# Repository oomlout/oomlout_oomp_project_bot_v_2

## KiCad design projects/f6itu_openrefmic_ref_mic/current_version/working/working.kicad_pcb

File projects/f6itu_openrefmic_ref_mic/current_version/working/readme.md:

# openrefmic
 
## summary 
* id: f6itu_openrefmic_ref_mic
* user: f6itu
* name: openrefmic
* board: ref_mic
* repo: https://github.com/F6ITU/OpenRefMic
* src_file_repo_kicad_pcb: preamplifier/ref_mic/ref_mic.kicad_pcb
* src_file_repo_kicad_pcb_link: https://github.com/F6ITU/OpenRefMic/tree/main/preamplifier/ref_mic/ref_mic.kicad_pcb
* src_file_repo_kicad_sch: preamplifier/ref_mic/ref_mic.kicad_sch
* src_file_repo_kicad_sch_link: https://github.com/F6ITU/OpenRefMic/tree/main/preamplifier/ref_mic/ref_mic.kicad_sch

* src_file_repo_sch: 
* src_file_repo_sch_link: https://github.com/F6ITU/OpenRefMic/tree/main/
* full details link: https://github.com/oomlout/oomlout_oomp_project_bot_v_2/tree/main/projects/f6itu_openrefmic_ref_mic/current_version/working

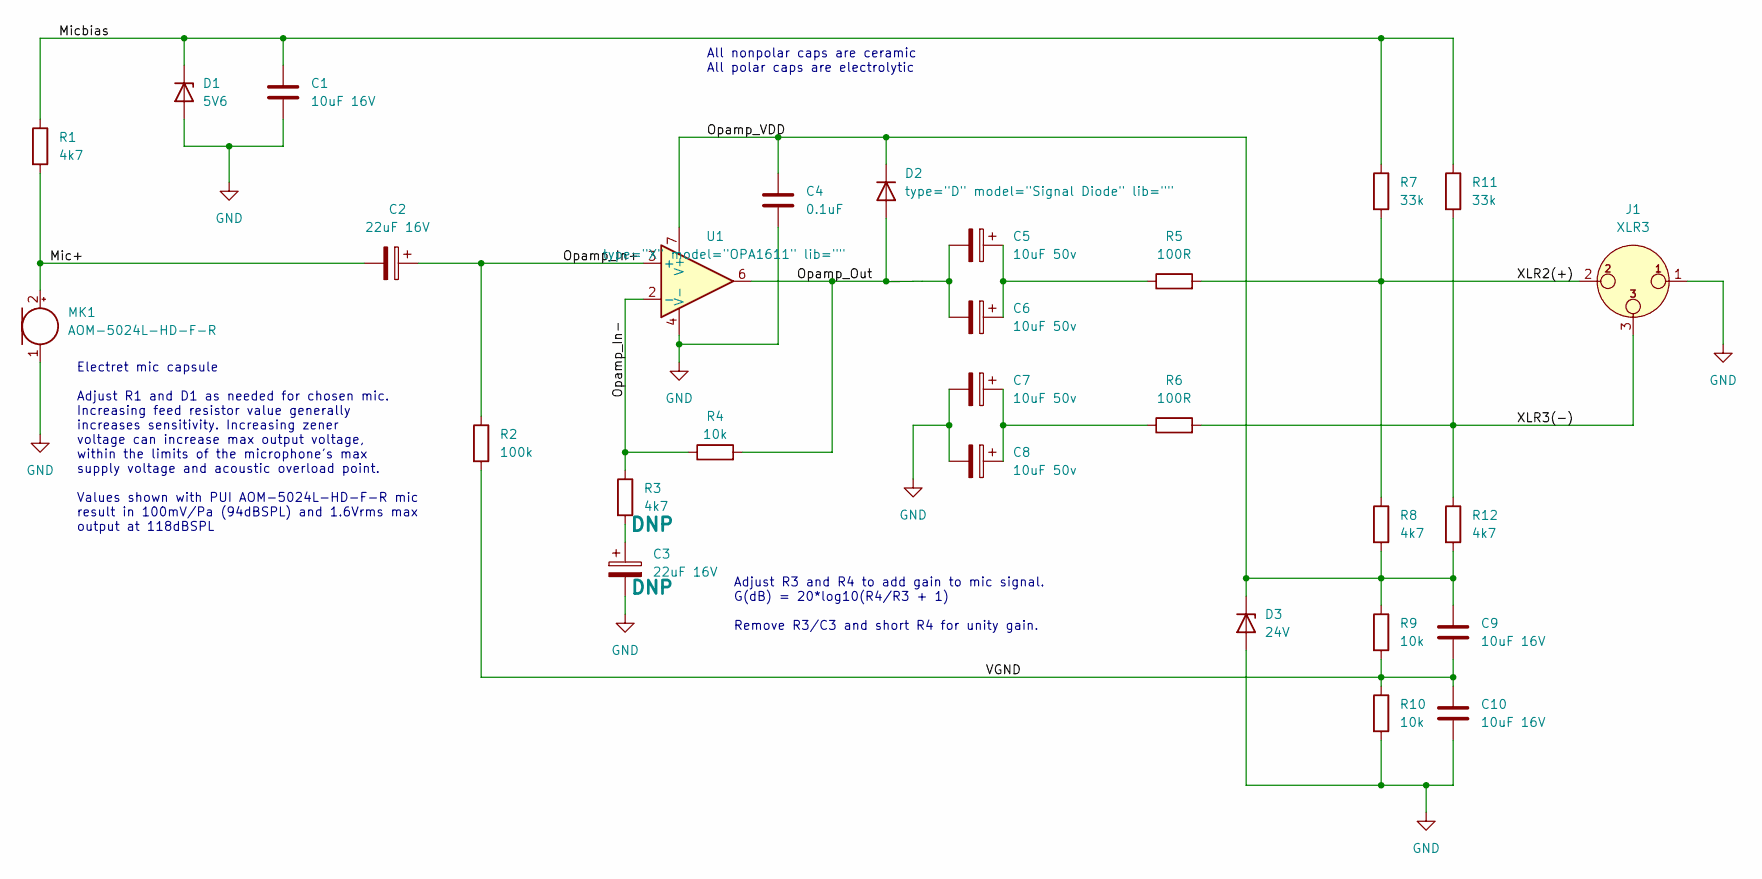
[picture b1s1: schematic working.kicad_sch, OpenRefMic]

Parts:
C1, C9, C10: 10uF 16V; C_0805_2012Metric_Pad1.18x1.45mm_HandSolder
C2, C3: 22uF 16V; CP_Elec_5x5.4
C4: 0.1uF; C_0603_1608Metric_Pad1.08x0.95mm_HandSolder
C5, C6, C7, C8: 10uF 50v; CP_Elec_6.3x5.4_Nichicon
D1: 5V6; SC-59_Handsoldering
D2: type="D" model="Signal Diode" lib=""; SOT-23_Handsoldering
D3: 24V; SOT-23_Handsoldering
J1: XLR3; PinHeader_1x03_P2.54mm_Vertical
MK1: AOM-5024L-HD-F-R; PinHeader_1x02_P2.54mm_Vertical
R1, R3, R8, R12: 4k7; R_0603_1608Metric_Pad0.98x0.95mm_HandSolder
R2: 100k; R_0603_1608Metric_Pad0.98x0.95mm_HandSolder
R4, R9, R10: 10k; R_0603_1608Metric_Pad0.98x0.95mm_HandSolder
R5, R6: 100R; R_0603_1608Metric_Pad0.98x0.95mm_HandSolder
R7, R11: 33k; R_0603_1608Metric_Pad0.98x0.95mm_HandSolder
U1: type="X" model="OPA1611" lib=""; SOIC-8_3.9x4.9mm_P1.27mm

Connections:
/Mic+: C2.2, MK1.2 (+), R1.2; also elsewhere on the board
/Micbias: C1.1, D1.3 (K), R1.1, R7.1, R11.1
/Opamp_In+: C2.1, R2.1, U1.3 (+)
/Opamp_In-: R3.1, R4.1, U1.2 (-)
/Opamp_Out: C5.2, C6.2, D2.1 (A), R4.2, U1.6
/Opamp_VDD: C4.1, C9.1, D2.3 (K), D3.3 (K), R8.2, R9.1, R12.2, U1.7 (V+)
/VGND: C9.2, C10.1, R2.2, R9.2, R10.1
/XLR2(+): J1.2, R5.2, R7.2, R8.1; also elsewhere on the board
/XLR3(-): J1.3, R6.2, R11.2, R12.1; also elsewhere on the board
GND: C1.2, C3.2, C4.2, C7.2, C8.2, C10.2, D1.1 (A), D3.1 (A), J1.1, MK1.1 (-), R10.2, U1.4 (V-); also elsewhere on the board
unnamed: C3.1, R3.2
unnamed: C5.1, C6.1, R5.1
unnamed: C7.1, C8.1, R6.1

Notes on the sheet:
All nonpolar caps are ceramic All polar caps are electrolytic
Adjust R3 and R4 to add gain to mic signal. G(dB) = 20*log10(R4/R3 + 1) Remove R3/C3 and short R4 for unity gain.
Electret mic capsule Adjust R1 and D1 as needed for chosen mic. Increasing feed resistor value generally increases sensitivity. Increasing zener voltage can increase max output voltage, within the limits of the microphone's max supply voltage and acoustic overload point. Values shown with PUI AOM-5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

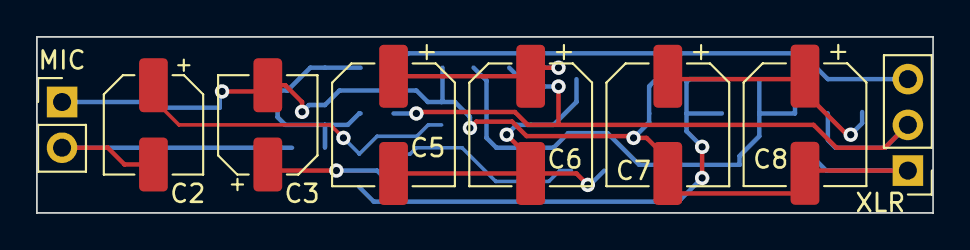
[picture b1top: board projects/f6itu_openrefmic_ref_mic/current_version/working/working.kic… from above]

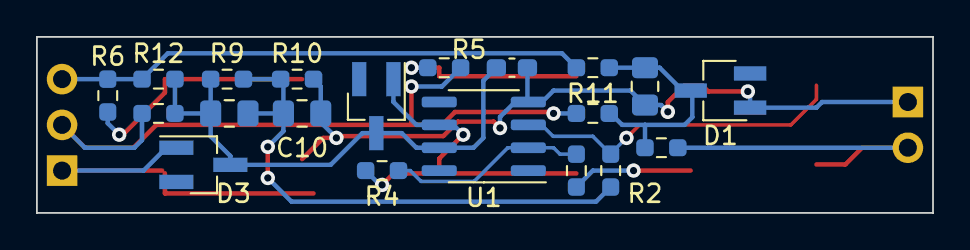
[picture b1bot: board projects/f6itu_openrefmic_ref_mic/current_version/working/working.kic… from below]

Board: 2 copper layers, 49.8 x 9.8 mm, 28 parts (20 on the bottom side), 13 nets.

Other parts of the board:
MIC: Microphone; PinHeader_1x02_P2.54mm_Vertical
XLR: XLR3; PinHeader_1x03_P2.54mm_Vertical

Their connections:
/Mic+: MIC.2 (+); also elsewhere on the board
/XLR2(+): XLR.2; also elsewhere on the board
/XLR3(-): XLR.3; also elsewhere on the board
GND: MIC.1 (-), XLR.1; also elsewhere on the board

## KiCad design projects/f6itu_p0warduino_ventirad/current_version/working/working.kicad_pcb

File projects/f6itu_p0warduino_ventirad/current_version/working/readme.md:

# p0warduino
 
## summary 
* id: f6itu_p0warduino_ventirad
* user: f6itu
* name: p0warduino
* board: ventirad
* repo: https://github.com/F6ITU/P0wArduino
* src_file_repo_kicad_pcb: ventirad.kicad_pcb
* src_file_repo_kicad_pcb_link: https://github.com/F6ITU/P0wArduino/tree/master/ventirad.kicad_pcb

* src_file_repo_sch: ventirad.sch
* src_file_repo_sch_link: https://github.com/F6ITU/P0wArduino/tree/master/ventirad.sch
* full details link: https://github.com/oomlout/oomlout_oomp_project_bot_v_2/tree/main/projects/f6itu_p0warduino_ventirad/current_version/working

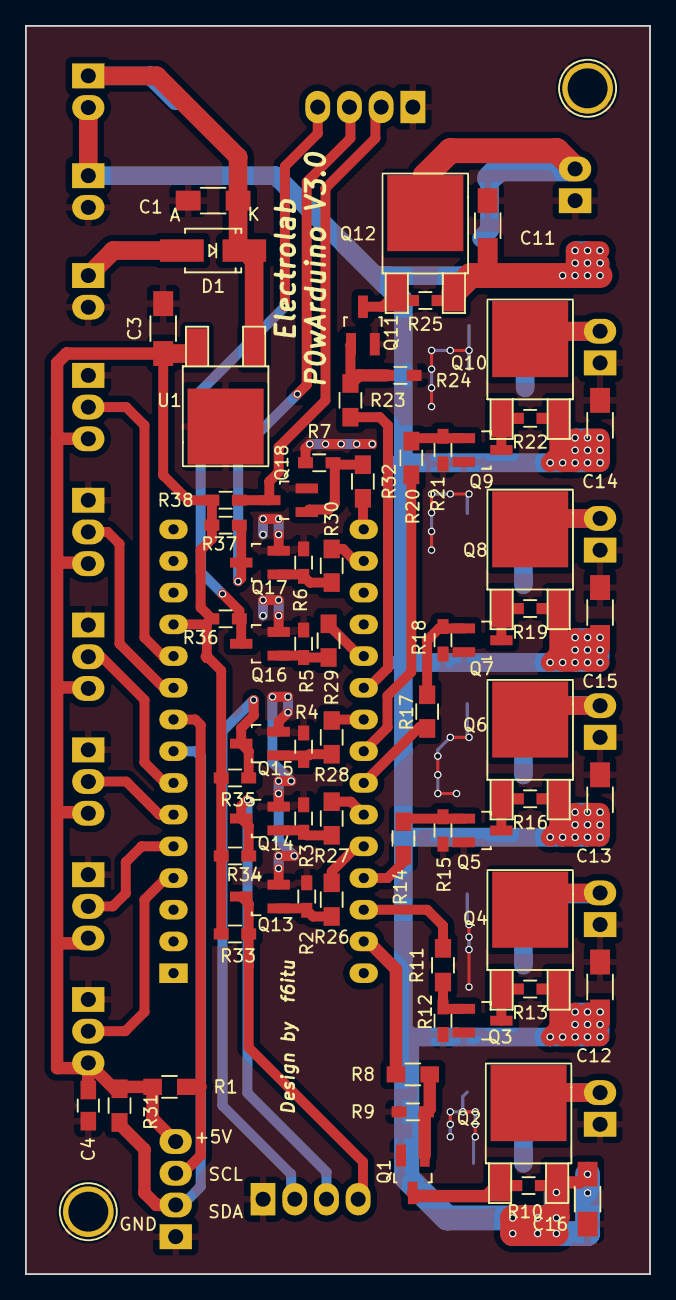
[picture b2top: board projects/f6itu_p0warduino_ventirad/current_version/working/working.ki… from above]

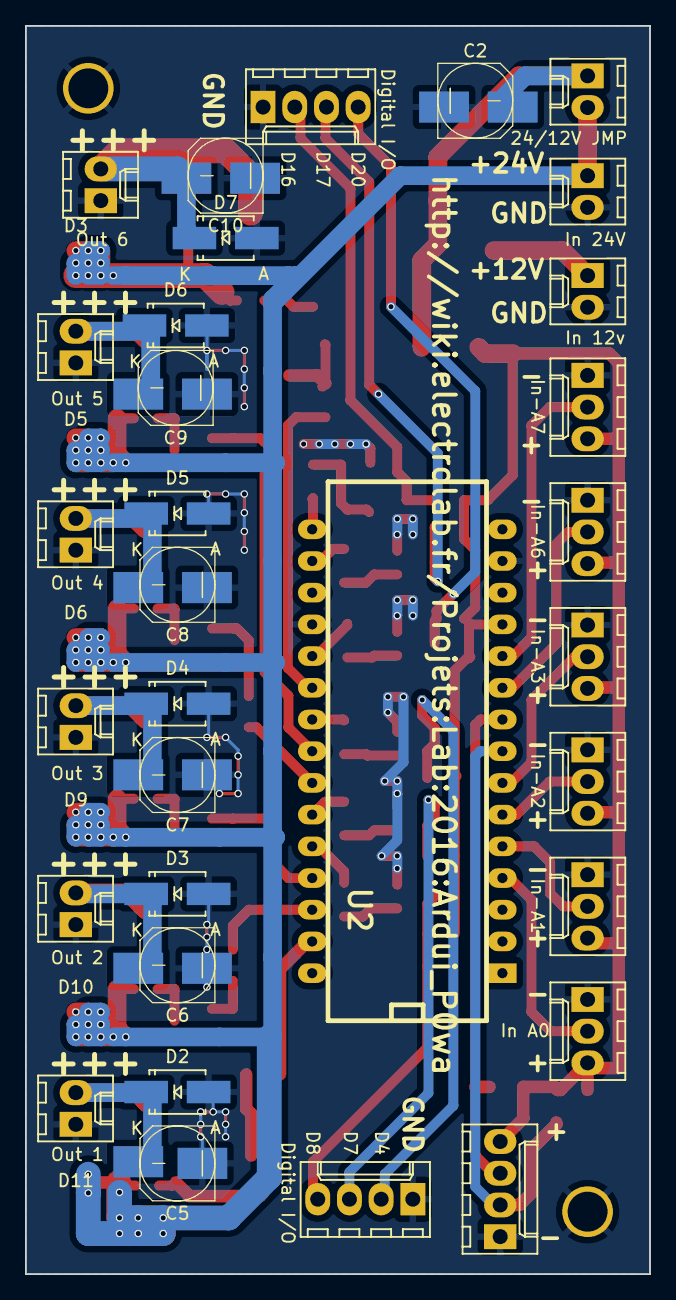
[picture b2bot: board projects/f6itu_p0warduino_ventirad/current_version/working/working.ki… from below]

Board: 2 copper layers, 50.0 x 100.0 mm, 81 parts (14 on the bottom side), 48 nets.

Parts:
C1, C3, C11, C12, C13, C14, C15, C16: 100n; C_1206_HandSoldering
C2: 200u; c_elec_6.3x7.7
C4: 10n; C_0805_HandSoldering
C5, C6, C7, C8, C9, C10: 100u; c_elec_6.3x7.7
D1, D2, D3, D4, D5, D6, D7: SS-26; SMA_Handsoldering
Q1, Q3, Q5, Q7, Q9, Q11, Q13, Q14, Q15, Q16, Q17, Q18: 2N7000; SOT-23_Handsoldering
Q2, Q4, Q6, Q8, Q10, Q12: IRFR9014; TO-252-2Lead
R1, R31: 10k; R_0805_HandSoldering
R2, R3, R4, R5, R6, R7, R9, R10, R12, R13, R15, R16, R18, R19, R21, R22, R24, R25, R33, R34, R35, R36, R37, R38: 10k; R_0603_HandSoldering
R8, R11, R14, R17, R20, R23, R26, R27, R28, R29, R30, R32: 1k; R_0805_HandSoldering
U1: LM7805; TO-252-2Lead
U2: http://wiki.electrolab.fr/Projets:Lab:2016:Ardui_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; arduino_nano

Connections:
+5V: C3.1, C4.1, R1.2, R31.2, R33.1, R34.1, R35.1, R36.1, R37.1, R38.1, U1.3, U2.12
+12V: C1.1, C2.1, D1.1, U1.1
GND: C1.2, C2.2, C3.2, C4.2, C5.2, C6.2, C7.2, C8.2, C9.2, C10.2, C11.1, C12.1, C13.1, C14.1, C15.1, C16.1, D2.2, D3.2, D4.2, D5.2, D6.2, D7.2, Q1.2, Q3.2, Q5.2, Q7.2, Q9.2, Q11.2, Q13.2, Q14.2, Q15.2, Q16.2, Q17.2, Q18.2, R2.2, R3.2, R4.2, R5.2, R6.2, R7.2, R9.2, R12.2, R15.2, R18.2, R21.2, R24.2, U1.2, U2.14, U2.19
unnamed: C5.1, D2.1, Q2.2
unnamed: C6.1, D3.1, Q4.2
unnamed: C7.1, D4.1, Q6.2
unnamed: C8.1, D5.1, Q8.2
unnamed: C9.1, D6.1, Q10.2
unnamed: C10.1, D7.1, Q12.2
unnamed: C11.2, C12.2, C13.2, C14.2, C15.2, C16.2, Q2.3, Q4.3, Q6.3, Q8.3, Q10.3, Q12.3, R10.1, R13.1, R16.1, R19.1, R22.1, R25.1
unnamed: R31.1, U2.8
unnamed: R1.1, U2.9
unnamed: Q15.3, R35.2
unnamed: Q14.3, R34.2
unnamed: Q13.3, R33.2
unnamed: Q18.3, R38.2
unnamed: Q17.3, R37.2
unnamed: Q16.3, R36.2
unnamed: Q1.1, R8.1, R9.1
unnamed: Q1.3, Q2.1, R10.2
unnamed: Q3.1, R11.1, R12.1
unnamed: Q3.3, Q4.1, R13.2
unnamed: Q5.1, R14.1, R15.1
unnamed: Q5.3, Q6.1, R16.2
unnamed: Q7.1, R17.1, R18.1
unnamed: Q7.3, Q8.1, R19.2
unnamed: Q9.1, R20.1, R21.1
unnamed: Q9.3, Q10.1, R22.2
unnamed: Q11.1, R23.1, R24.1
unnamed: Q11.3, Q12.1, R25.2
unnamed: Q13.1, R2.1, R26.1
unnamed: Q14.1, R3.1, R27.1
unnamed: Q15.1, R4.1, R28.1
unnamed: Q16.1, R5.1, R29.1
unnamed: Q17.1, R6.1, R30.1
unnamed: Q18.1, R7.1, R32.1
unnamed: R8.2, U2.29
unnamed: R11.2, U2.28
unnamed: R14.2, U2.27
unnamed: R17.2, U2.24
unnamed: R20.2, U2.23
unnamed: R23.2, U2.21
unnamed: R26.2, U2.26
unnamed: R27.2, U2.25
unnamed: R28.2, U2.22
unnamed: R29.2, U2.20
unnamed: R30.2, U2.17
unnamed: R32.2, U2.16

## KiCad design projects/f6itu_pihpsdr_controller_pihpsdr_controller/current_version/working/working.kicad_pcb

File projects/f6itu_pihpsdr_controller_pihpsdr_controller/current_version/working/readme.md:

# pihpsdr_controller
 
## summary 
* id: f6itu_pihpsdr_controller_pihpsdr_controller
* user: f6itu
* name: pihpsdr_controller
* board: pihpsdr_controller
* repo: https://github.com/F6ITU/piHPSDR_Controller
* src_file_repo_kicad_pcb: piHPSDR_Controller.kicad_pcb
* src_file_repo_kicad_pcb_link: https://github.com/F6ITU/piHPSDR_Controller/tree/master/piHPSDR_Controller.kicad_pcb

* src_file_repo_sch: 
* src_file_repo_sch_link: https://github.com/F6ITU/piHPSDR_Controller/tree/master/
* full details link: https://github.com/oomlout/oomlout_oomp_project_bot_v_2/tree/main/projects/f6itu_pihpsdr_controller_pihpsdr_controller/current_version/working

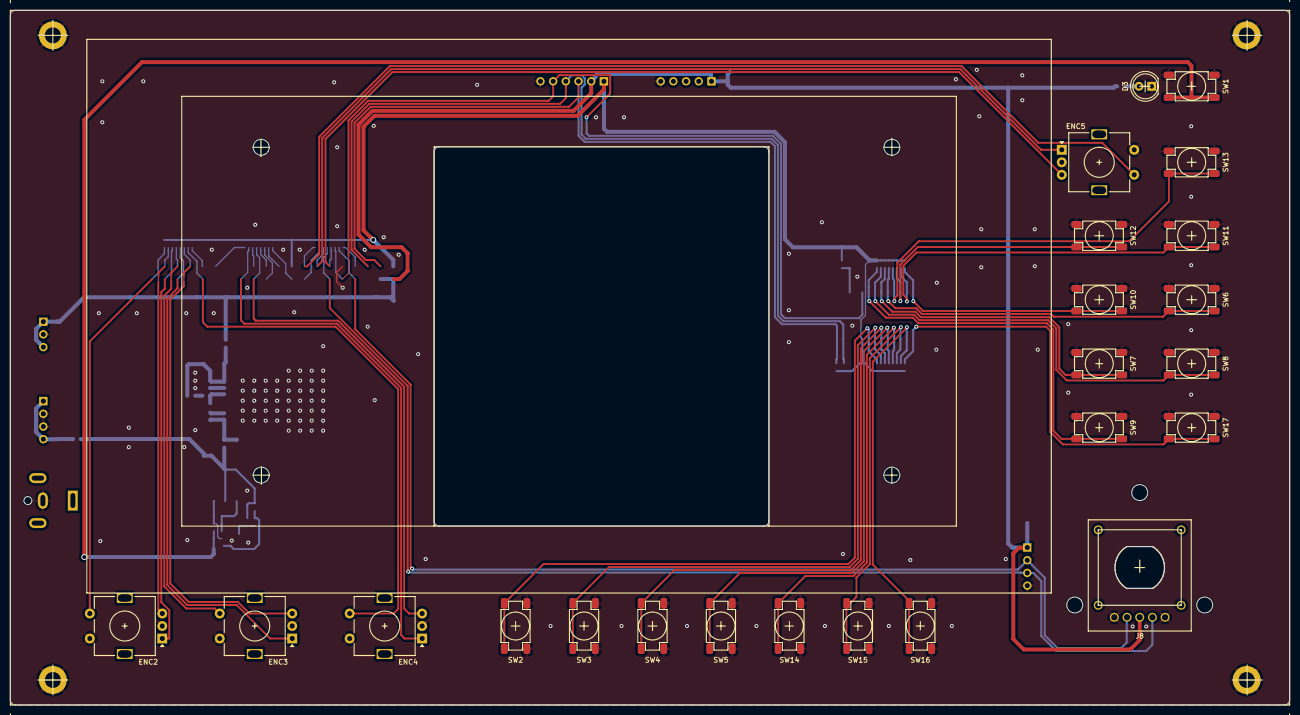
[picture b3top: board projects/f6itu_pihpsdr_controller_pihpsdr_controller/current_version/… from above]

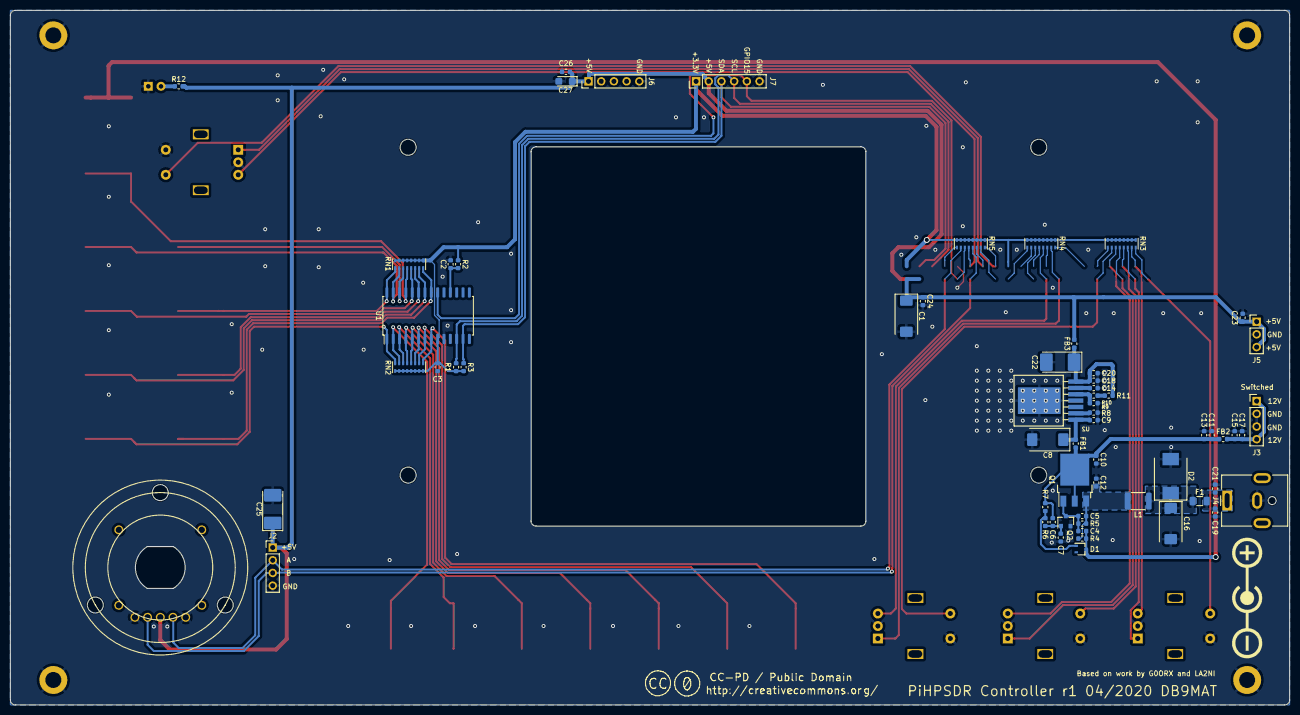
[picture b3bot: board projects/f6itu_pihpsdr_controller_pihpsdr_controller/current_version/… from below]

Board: 2 copper layers, 256.0 x 139.0 mm, 88 parts (61 on the bottom side), 53 nets.

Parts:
 : MountingHole_3.2mm_M3_DIN965_Pad
 #2,  #3,  #4: MountingHole_3.2mm_M3_DIN965_Pad
C1: 220u/10V; CP_EIA-7343-31_Kemet-D
C2: 1n; C_0603_1608Metric
C3, C10, C12, C20, C21, C24, C26: 10u; C_0603_1608Metric
C4, C13, C17: 1u; C_0603_1608Metric
C5, C6, C7, C9, C11, C14, C15, C18, C19, C23: 100n; C_0603_1608Metric
C8: 47u/35V; CP_EIA-7343-43_Kemet-X
C16: 22u/35V; CP_EIA-7343-31_Kemet-D
C22, C25: 100u/10V; CP_EIA-7132-28_AVX-C
C27: 100u/6.3V; CP_EIA-3216-18_Kemet-A
D1: BAS16J; SOT-323_SC-70
D2: SK54; D_SMC
D3: Green; LED_D5.0mm
ENC2, ENC3, ENC4, ENC5: Rotary_Encoder_Switch; RotaryEncoder_Alps_EC11E-Switch_Vertical_H20mm
F1: 5A; Fuse_1206_3216Metric
FB1, FB2, FB3: TBD; L_0603_1608Metric
J2: ENC1; PinHeader_1x04_P2.54mm_Vertical
J3: 12V_SWITCHED; PinHeader_1x04_P2.54mm_Vertical
J4: 12V_IN; BarrelJack_CUI_PJ-063AH_Horizontal
J5: 5V/3A; PinHeader_1x03_P2.54mm_Vertical
J6: TO_DISPLAY; PinHeader_1x05_P2.54mm_Vertical
J7: Conn_01x06; PinHeader_1x06_P2.54mm_Vertical
J8: ENC1a; HRPG-AXXX
L1: 74279226101; L_1812_4532Metric
Q1: FDD6685; TO-252-3_TabPin2
Q2: 2N7002K; SOT-23
R1, R3, R4: 10k; R_0603_1608Metric
R2, R5, R7: 100k; R_0603_1608Metric
R6: 180k; R_0603_1608Metric
R8, R12: 1k5; R_0603_1608Metric
R9: 620; R_0603_1608Metric
R10: 3k3; R_0603_1608Metric
R11: 47; R_0603_1608Metric
RN1, RN2, RN3, RN4, RN5: 10k; R_Cat16-8
SW1: ON_OFF; TL3301AF160QG
SW2, SW3, SW4, SW5, SW6, SW7, SW8, SW9, SW10, SW11, SW12, SW13, SW14, SW15, SW16, SW17: SW_Push; TL3301AF160QG
U1: MCP23017_SO; SOIC-28W_7.5x17.9mm_P1.27mm
U2: LMZ22005; 7TO-PMOD

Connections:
+3V3: C3.1, J7.1, R1.2, R2.1, R3.1, RN1.1, RN2.1, RN3.1, RN4.1, RN5.1, U1.9
+5V: C1.1, C23.1, C24.1, C25.1, C26.1, C27.1, FB3.2, J2.1, J5.1, J5.3, J6.1, J7.2, J8.3, R12.2
+12V: C6.1, C10.1, C11.1, C13.1, FB1.2, FB2.2, Q1.2, R7.1
/Raspberry Pi/GPIO2: J7.3, R3.2, U1.13
/Raspberry Pi/GPIO3: J7.4, R1.1, U1.12
GND: .1, #2.1, #3.1, #4.1, C1.2, C2.2, C3.2, C7.2, C8.2, C9.2, C10.2, C11.2, C12.2, C13.2, C14.2, C15.2, C16.2, C17.2, C18.2, C19.2, C20.2, C21.2, C22.2, C23.2, C24.2, C25.2, C26.2, C27.2, D2.2, D3.1, ENC2.C, ENC2.S2, ENC3.C, ENC3.S2, ENC4.C, ENC4.S2, ENC5.C, ENC5.S2, J2.4, J3.2, J3.3, J4.2, J5.2, J6.5, J7.6, J8.1, J8.5, Q2.2, R8.1, R9.1, SW1.1, SW2.1, SW3.1, SW4.1, SW5.1, SW6.1, SW7.1, SW8.1, SW9.1, SW10.1, SW11.1, SW12.1, SW13.1, SW14.1, SW15.1, SW16.1, SW17.1, U1.10, U2.4, U2.8
GPA0: RN1.2, SW9.2, U1.21
GPA1: RN1.3, SW8.2, U1.22
GPA2: RN1.4, SW7.2, U1.23
GPA3: RN1.5, SW6.2, U1.24
GPA4: RN1.6, SW13.2, U1.25
GPA5: RN1.7, SW12.2, U1.26
GPA6: RN1.8, SW11.2, U1.27
GPA7: RN1.9, SW10.2, U1.28
GPB0: RN2.2, SW17.2, U1.1
GPB1: RN2.3, SW16.2, U1.2
GPB2: RN2.4, SW15.2, U1.3
GPB3: RN2.5, SW14.2, U1.4
GPB4: RN2.6, SW5.2, U1.5
GPB5: RN2.7, SW4.2, U1.6
GPB6: RN2.8, SW3.2, U1.7
GPB7: RN2.9, SW2.2, U1.8
GPIO7: ENC4.A, RN4.3
GPIO8: ENC4.B, RN4.5
GPIO12: ENC4.S1, RN3.8
GPIO13: ENC3.B, RN3.7
GPIO14: J2.2, J8.4, RN5.8
GPIO15: J7.5, RN5.7, U1.20
GPIO16: ENC3.A, RN3.6
GPIO17: ENC5.B, RN5.6
GPIO18: J2.3, J8.2, RN5.5
GPIO19: ENC3.S1, RN3.5
GPIO20: ENC2.A, RN3.4
GPIO21: ENC2.S1, RN3.2
GPIO22: ENC5.S1, RN5.2
GPIO26: ENC2.B, RN3.3
GPIO27: ENC5.A, RN5.4
unnamed: C2.1, R2.2, U1.18
unnamed: C4.1, C5.2, Q1.1, Q2.3, R5.2
unnamed: C4.2, D1.3, R4.2, SW1.2
unnamed: C6.2, C7.1, Q2.1, R6.2
unnamed: C8.1, C9.1, FB1.1, U2.1
unnamed: C5.1, C12.1, L1.1, Q1.3, R4.1, R5.1
unnamed: C14.1, U2.6
unnamed: C15.1, C17.1, FB2.1, J3.1, J3.4
unnamed: C16.1, D2.1, F1.1, L1.2
unnamed: C18.1, C20.1, C22.1, FB3.1, R11.2, U2.7
unnamed: C19.1, C21.1, F1.2, J4.1
unnamed: D1.1, R6.1, R7.2
unnamed: D3.2, R12.1
unnamed: R8.2, U2.2
unnamed: R9.2, R10.1, U2.5
unnamed: R10.2, R11.1

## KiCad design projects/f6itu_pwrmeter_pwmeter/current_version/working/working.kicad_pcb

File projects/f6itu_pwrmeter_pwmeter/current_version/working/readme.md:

# pwrmeter
 
## summary 
* id: f6itu_pwrmeter_pwmeter
* user: f6itu
* name: pwrmeter
* board: pwmeter
* repo: https://github.com/F6ITU/PWRmeter
* src_file_repo_kicad_pcb: PWMeter.kicad_pcb
* src_file_repo_kicad_pcb_link: https://github.com/F6ITU/PWRmeter/tree/master/PWMeter.kicad_pcb

* src_file_repo_sch: PWMeter.sch
* src_file_repo_sch_link: https://github.com/F6ITU/PWRmeter/tree/master/PWMeter.sch
* full details link: https://github.com/oomlout/oomlout_oomp_project_bot_v_2/tree/main/projects/f6itu_pwrmeter_pwmeter/current_version/working

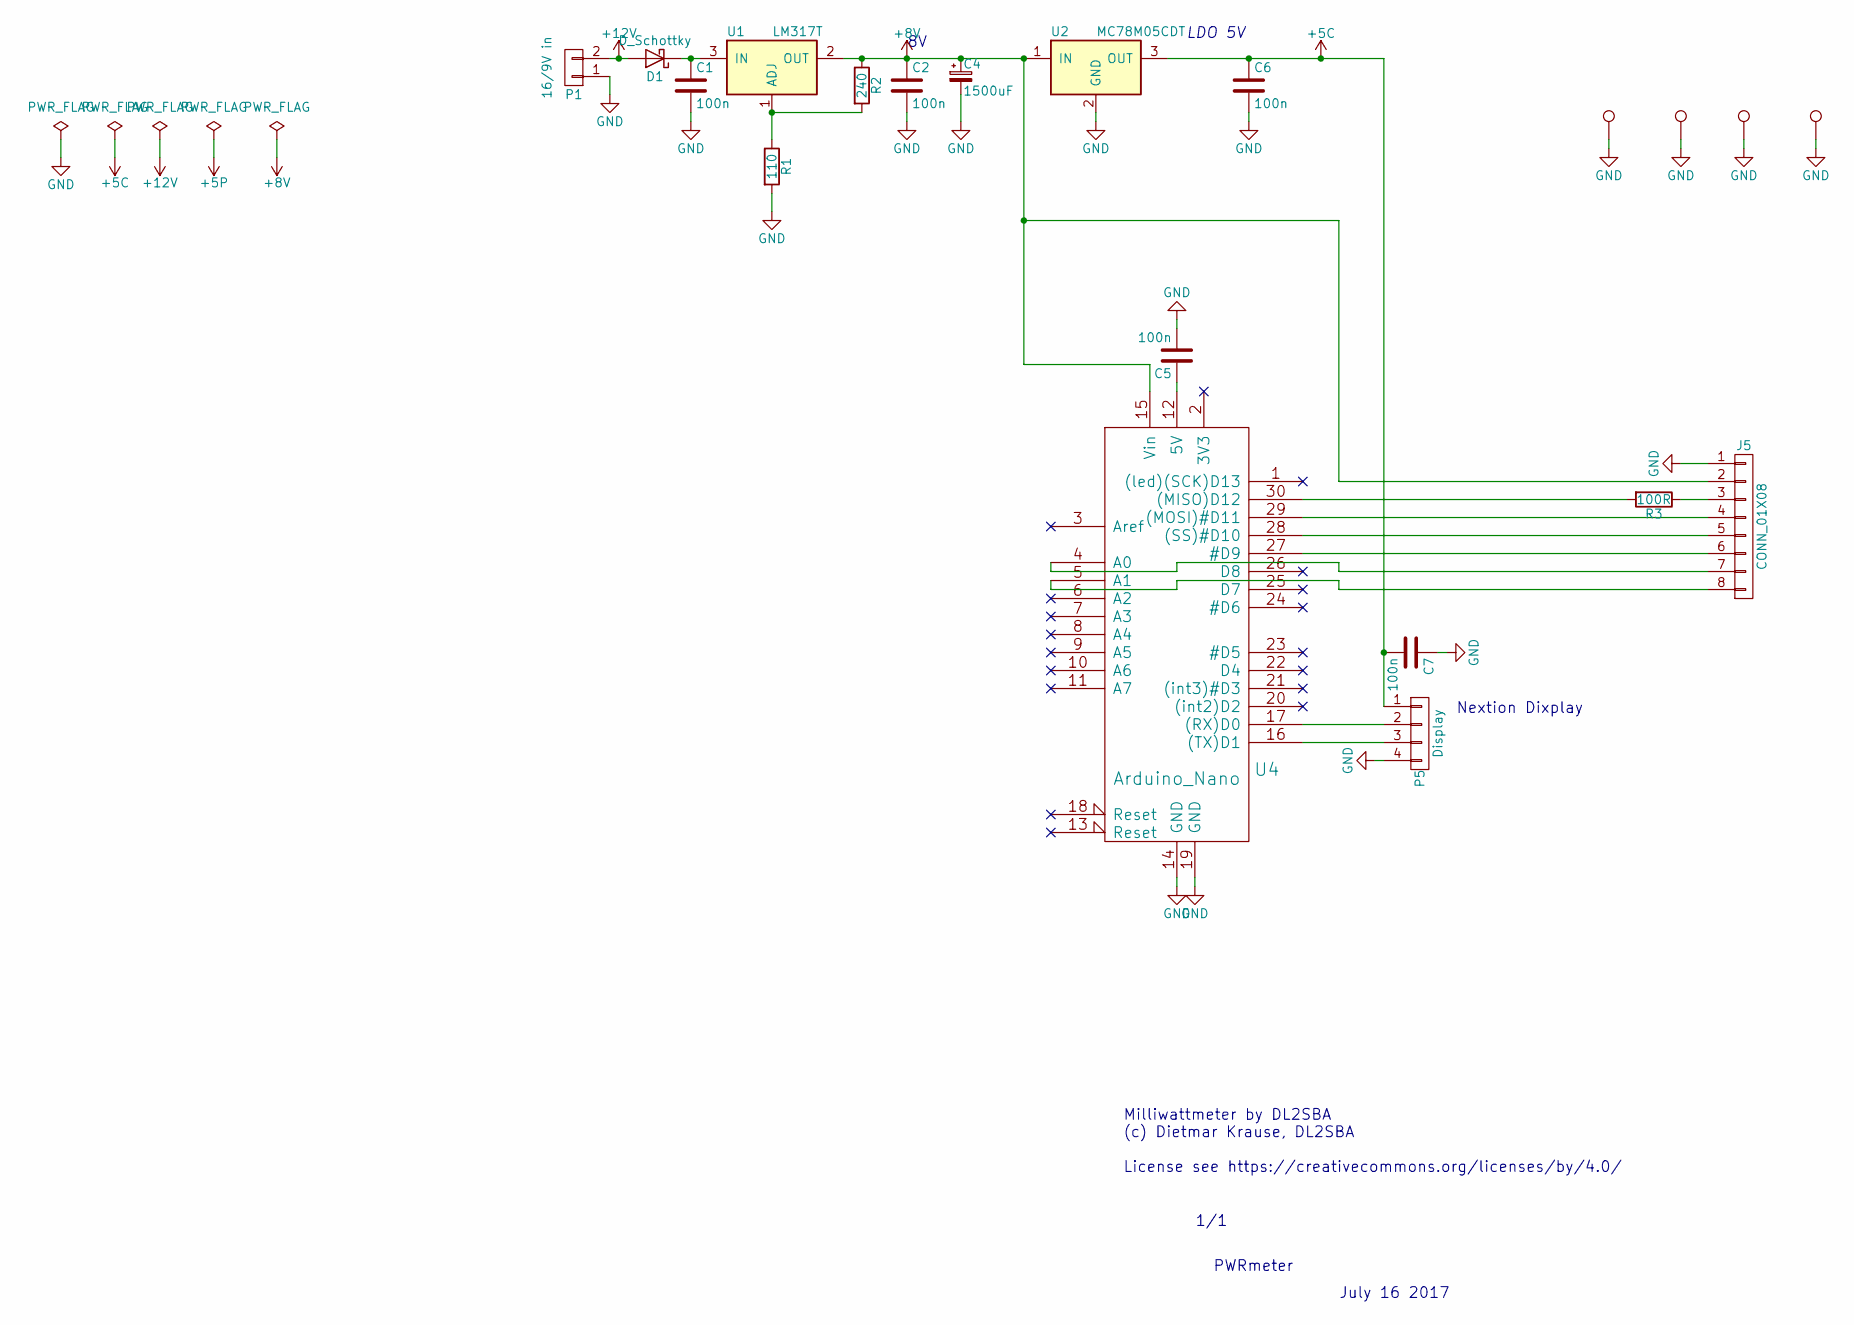
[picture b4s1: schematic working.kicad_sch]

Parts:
C1, C2, C5, C6, C7: 100n; C_1206_HandSoldering
C4: 1500uF; c_elec_6.3x7.7
D1: D_Schottky; SMB_Handsoldering
J1, J2, J3, J4: TEST_1P; MountingHole_3.2mm_M3_Pad
J5: CONN_01X08; kk100_22-23-2081
P1: 16/9V in; Molex_KK-6410-02_02x2.54mm_Straight
P5: Display; Molex_KK-6410-04_04x2.54mm_Straight
R1: 110; C_0805_HandSoldering
R2: 240; C_0805_HandSoldering
R3: 100R; R_0805_HandSoldering
U1: LM317T; TO-220_Neutral123_Horizontal_LargePads
U2: MC78M05CDT; TO-252-2Lead
U4: Arduino_Nano; arduino_nano

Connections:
+5C: C6.1, C7.2, P5.1, U2.3 (OUT)
+8V: C2.1, C4.1, J5.2, R2.1, U1.2 (OUT), U2.1 (IN), U4.15 (Vin)
+12V: D1.2 (A), P1.2
GND: C1.2, C2.2, C4.2, C5.2, C6.2, C7.1, J1.1, J2.1, J3.1, J4.1, J5.1, P1.1, P5.4, R1.2, U2.2 (GND), U4.14 (GND), U4.19 (GND)
unnamed: C1.1, D1.1 (K), U1.3 (IN)
unnamed: C5.1, U4.12 (5V)
unnamed: J5.3, R3.1
unnamed: J5.4, U4.29 ((MOSI)#D11)
unnamed: J5.5, U4.28 ((SS)#D10)
unnamed: J5.6, U4.27 (#D9)
unnamed: J5.7, U4.4 (A0)
unnamed: J5.8, U4.5 (A1)
unnamed: P5.2, U4.17 ((RX)D0)
unnamed: P5.3, U4.16 ((TX)D1)
unnamed: R1.1, R2.2, U1.1 (ADJ)
unnamed: R3.2, U4.30 ((MISO)D12)

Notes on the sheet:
Nextion Dixplay
LDO 5V
PWRmeter
Milliwattmeter by DL2SBA (c) Dietmar Krause, DL2SBA License see https://creativecommons.org/licenses/by/4.0/
1/1
July 16 2017

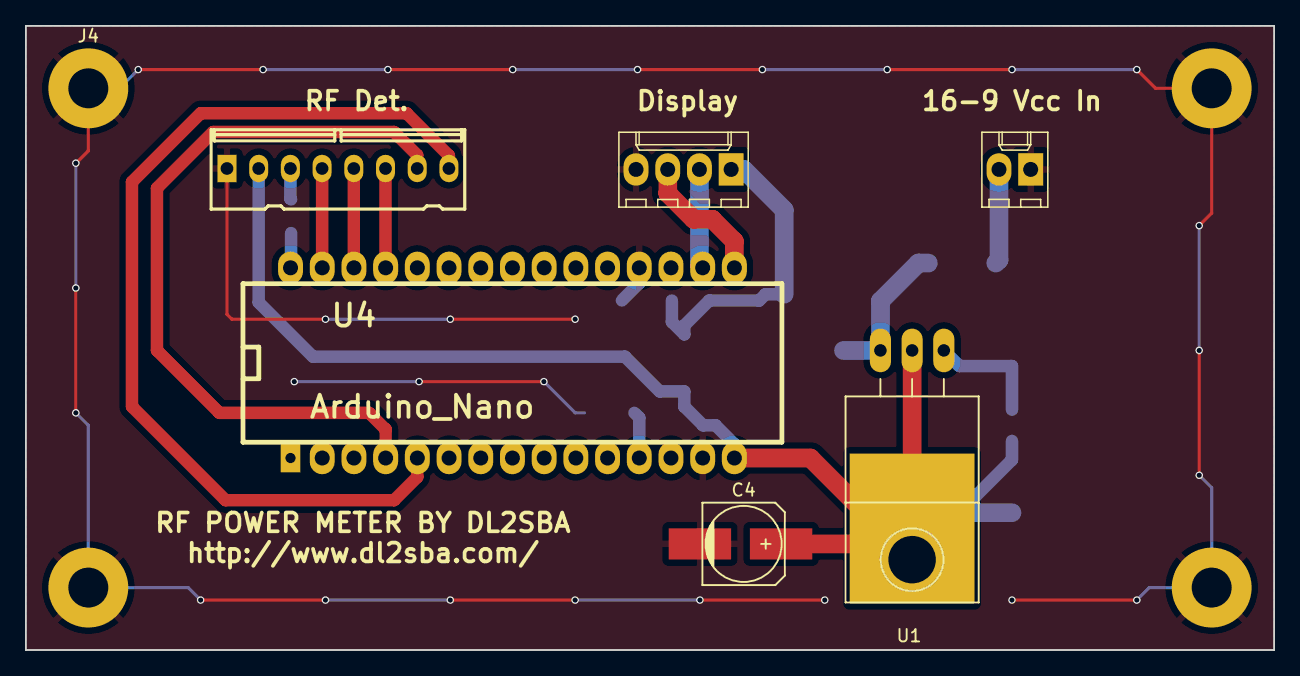
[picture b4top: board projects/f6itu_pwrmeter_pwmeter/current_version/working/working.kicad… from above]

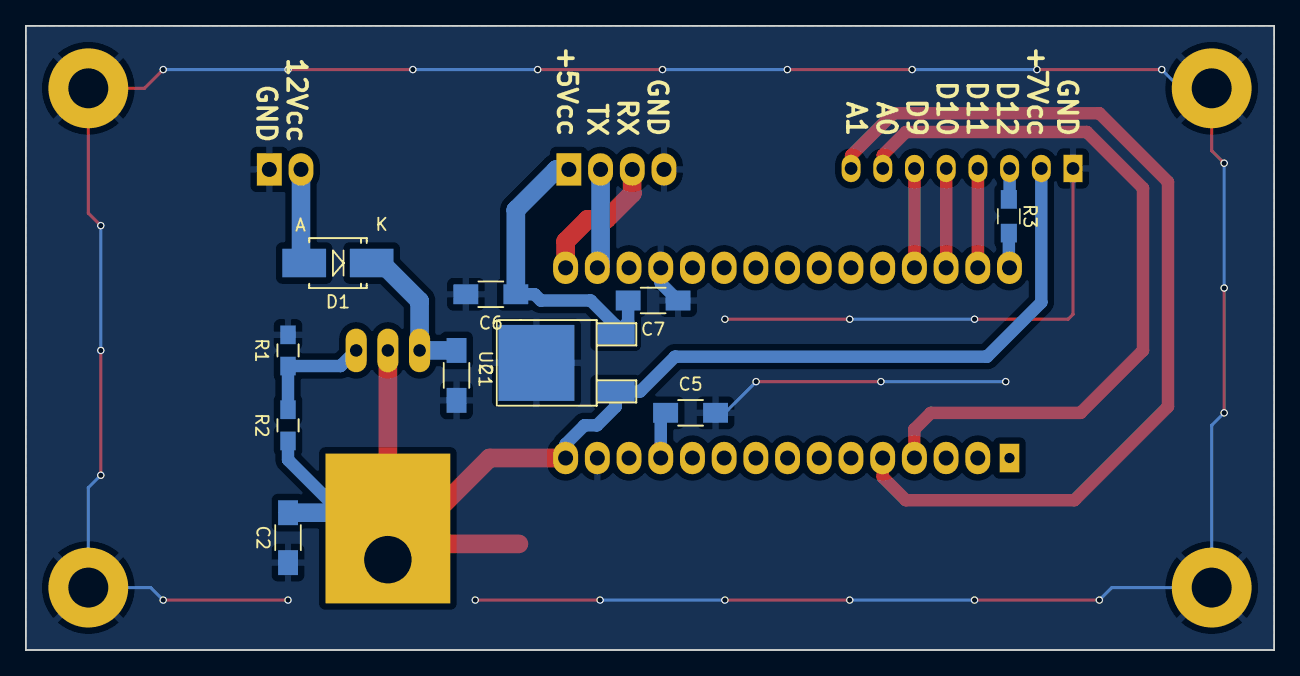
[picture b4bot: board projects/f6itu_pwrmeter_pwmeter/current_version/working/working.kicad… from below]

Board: 2 copper layers, 100.0 x 50.0 mm, 20 parts (10 on the bottom side), 16 nets.

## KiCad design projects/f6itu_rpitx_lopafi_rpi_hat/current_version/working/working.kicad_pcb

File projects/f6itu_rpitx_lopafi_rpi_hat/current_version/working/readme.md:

# rpitx_lopafi
 
## summary 
* id: f6itu_rpitx_lopafi_rpi_hat
* user: f6itu
* name: rpitx_lopafi
* board: rpi_hat
* repo: https://github.com/F6ITU/rpitx_lopafi
* src_file_repo_kicad_pcb: RPi_Hat.kicad_pcb
* src_file_repo_kicad_pcb_link: https://github.com/F6ITU/rpitx_lopafi/tree/master/RPi_Hat.kicad_pcb

* src_file_repo_sch: 
* src_file_repo_sch_link: https://github.com/F6ITU/rpitx_lopafi/tree/master/
* full details link: https://github.com/oomlout/oomlout_oomp_project_bot_v_2/tree/main/projects/f6itu_rpitx_lopafi_rpi_hat/current_version/working

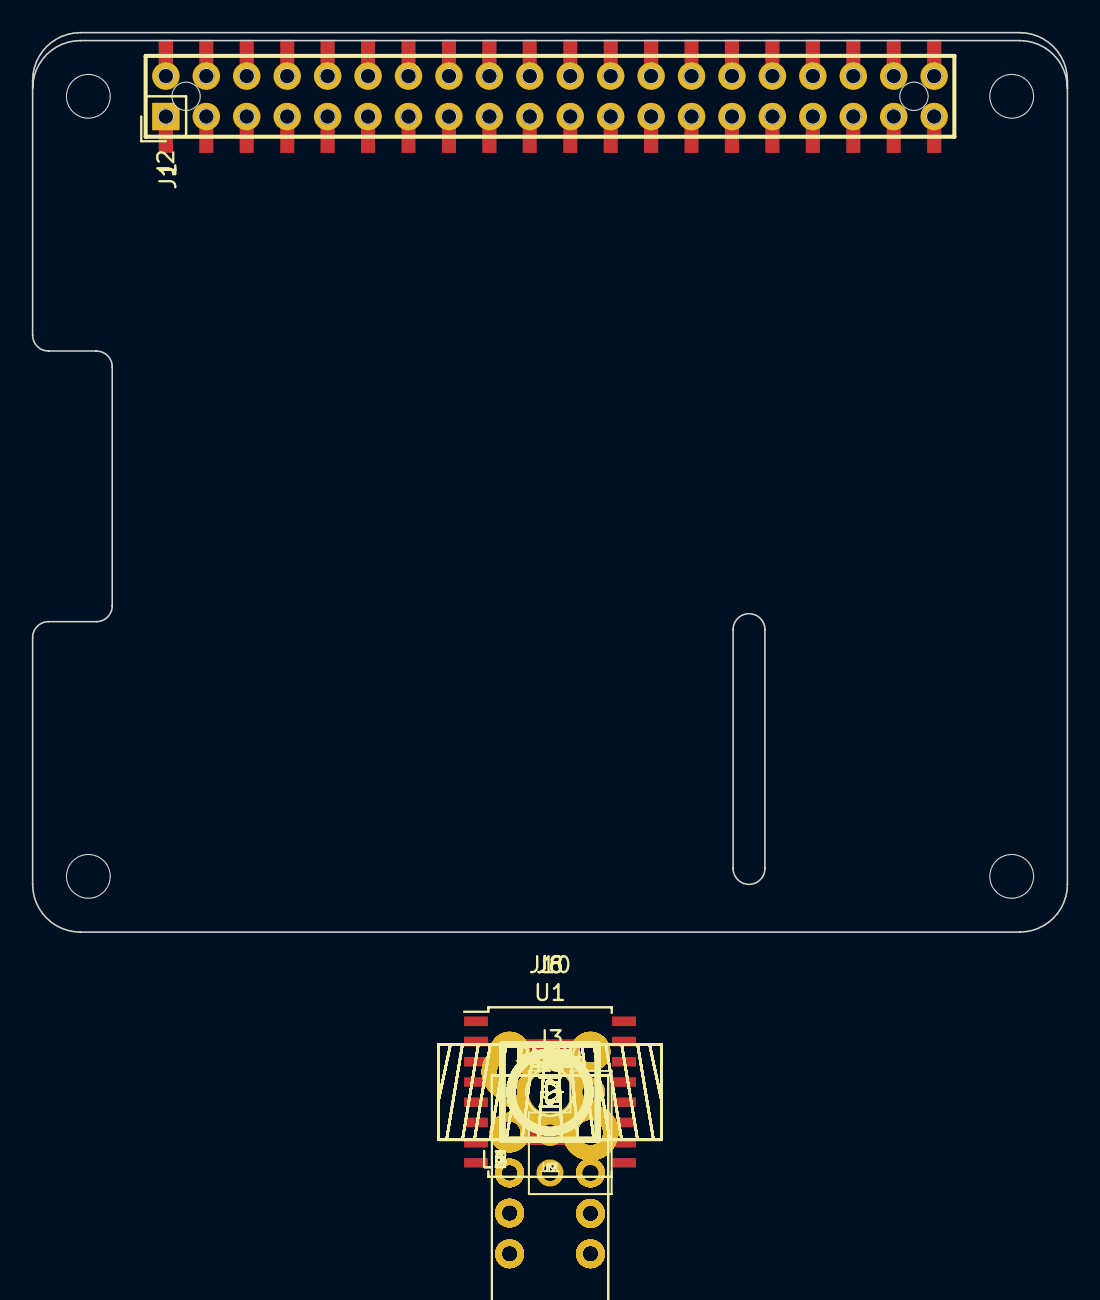
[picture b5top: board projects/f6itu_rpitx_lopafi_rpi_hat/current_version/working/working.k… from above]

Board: 2 copper layers, 65.0 x 56.5 mm, 51 parts (0 on the bottom side), 26 nets, no tracks yet.

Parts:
C1, C2, C3, C4, C5, C6, C7, C8, C9, C10, C11, C13, C14, C15, C16, C17, C18, C19, C20, C21, C22: C_Small; C_1206_3216Metric_Pad1.24x1.80mm_HandSolder
C12: 100n; C_1206_3216Metric_Pad1.24x1.80mm_HandSolder
J1: RPi_GPIO; Samtec_HLE-120-02-XXX-DV-BE-XX-XX
J2: Conn_01x01; Pin_Header_Straight_2x20
J3: Conn_01x01; MountingHole_2.7mm_M2.5_DIN965_Pad
J4: Conn_02x03_Odd_Even; PinHeader_2x03_P2.54mm_Vertical
J6, J8, J10: Conn_Coaxial; SMA_EDGE_NRW
J7, J9, J11: Conn_Coaxial; SMA_PINS
L1, L2, L3, L4, L5, L6: L_Small; T50_V_THT
R1, R2, R3, R4, R5, R6: 4k7; R_0805_2012Metric_Pad1.15x1.50mm_HandSolder
RL1, RL2, RL3, RL4, RL5, RL6: EC2-5NU; Relay_DPDT_NEC_EC2
U1: TCA9534; SOIC-16W_7.5x10.3mm_P1.27mm

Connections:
2.5MHz: RL1.12, RL2.12, U1.4
5V: C1.1, C2.2, C8.1, C9.2, C12.2, C16.1, C17.2, J4.1, J4.3, J4.5, R1.1, R2.1, R3.1, RL1.1, RL2.1, RL3.1, RL4.1, RL5.1, RL6.1, U1.16
6MHz: RL3.12, RL4.12, U1.5
12MHz: RL5.12, RL6.12, U1.6
GND: C1.2, C2.1, C5.2, C6.2, C7.2, C8.2, C9.1, C12.1, C13.2, C14.2, C15.2, C16.2, C17.1, C20.2, C21.2, C22.2, J2.1, J3.1, R4.2, R5.2, R6.2, RL1.3, RL1.10, RL2.3, RL2.10, RL3.3, RL3.10, RL4.3, RL4.10, RL5.3, RL5.10, RL6.3, RL6.10, U1.8
unnamed: C3.1, C4.2, C6.1, L1.2, L2.1
unnamed: C3.2, C5.1, L1.1, RL1.4, RL1.9
unnamed: C4.1, C7.1, L2.2, RL2.4, RL2.9
unnamed: C10.1, C11.2, C14.1, L3.2, L4.1
unnamed: C10.2, C13.1, L3.1, RL3.4, RL3.9
unnamed: C11.1, C15.1, L4.2, RL4.4, RL4.9
unnamed: C18.1, C19.2, C21.1, L5.2, L6.1
unnamed: C18.2, C20.1, L5.1, RL5.4, RL5.9
unnamed: C19.1, C22.1, L6.2, RL6.4, RL6.9
unnamed: J4.2, R4.1, U1.1
unnamed: J4.4, R5.1, U1.2
unnamed: J4.6, R6.1, U1.3
unnamed: J6.1, J7.1
unnamed: J6.2, J7.2
unnamed: J8.1, J9.1, RL1.5, RL1.8, RL3.5, RL3.8, RL5.5, RL5.8
unnamed: J8.2, J9.2
unnamed: J10.1, J11.1, RL2.5, RL2.8, RL4.5, RL4.8, RL6.5, RL6.8
unnamed: J10.2, J11.2
unnamed: R3.2, U1.13
SCL: R1.2, U1.14
SDA: R2.2, U1.15

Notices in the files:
projects/f6itu_openrefmic_ref_mic/current_version/working/working.kicad_sch:
Loudifier - MIT license - https://github.com/loudifier/OpenRefMic
